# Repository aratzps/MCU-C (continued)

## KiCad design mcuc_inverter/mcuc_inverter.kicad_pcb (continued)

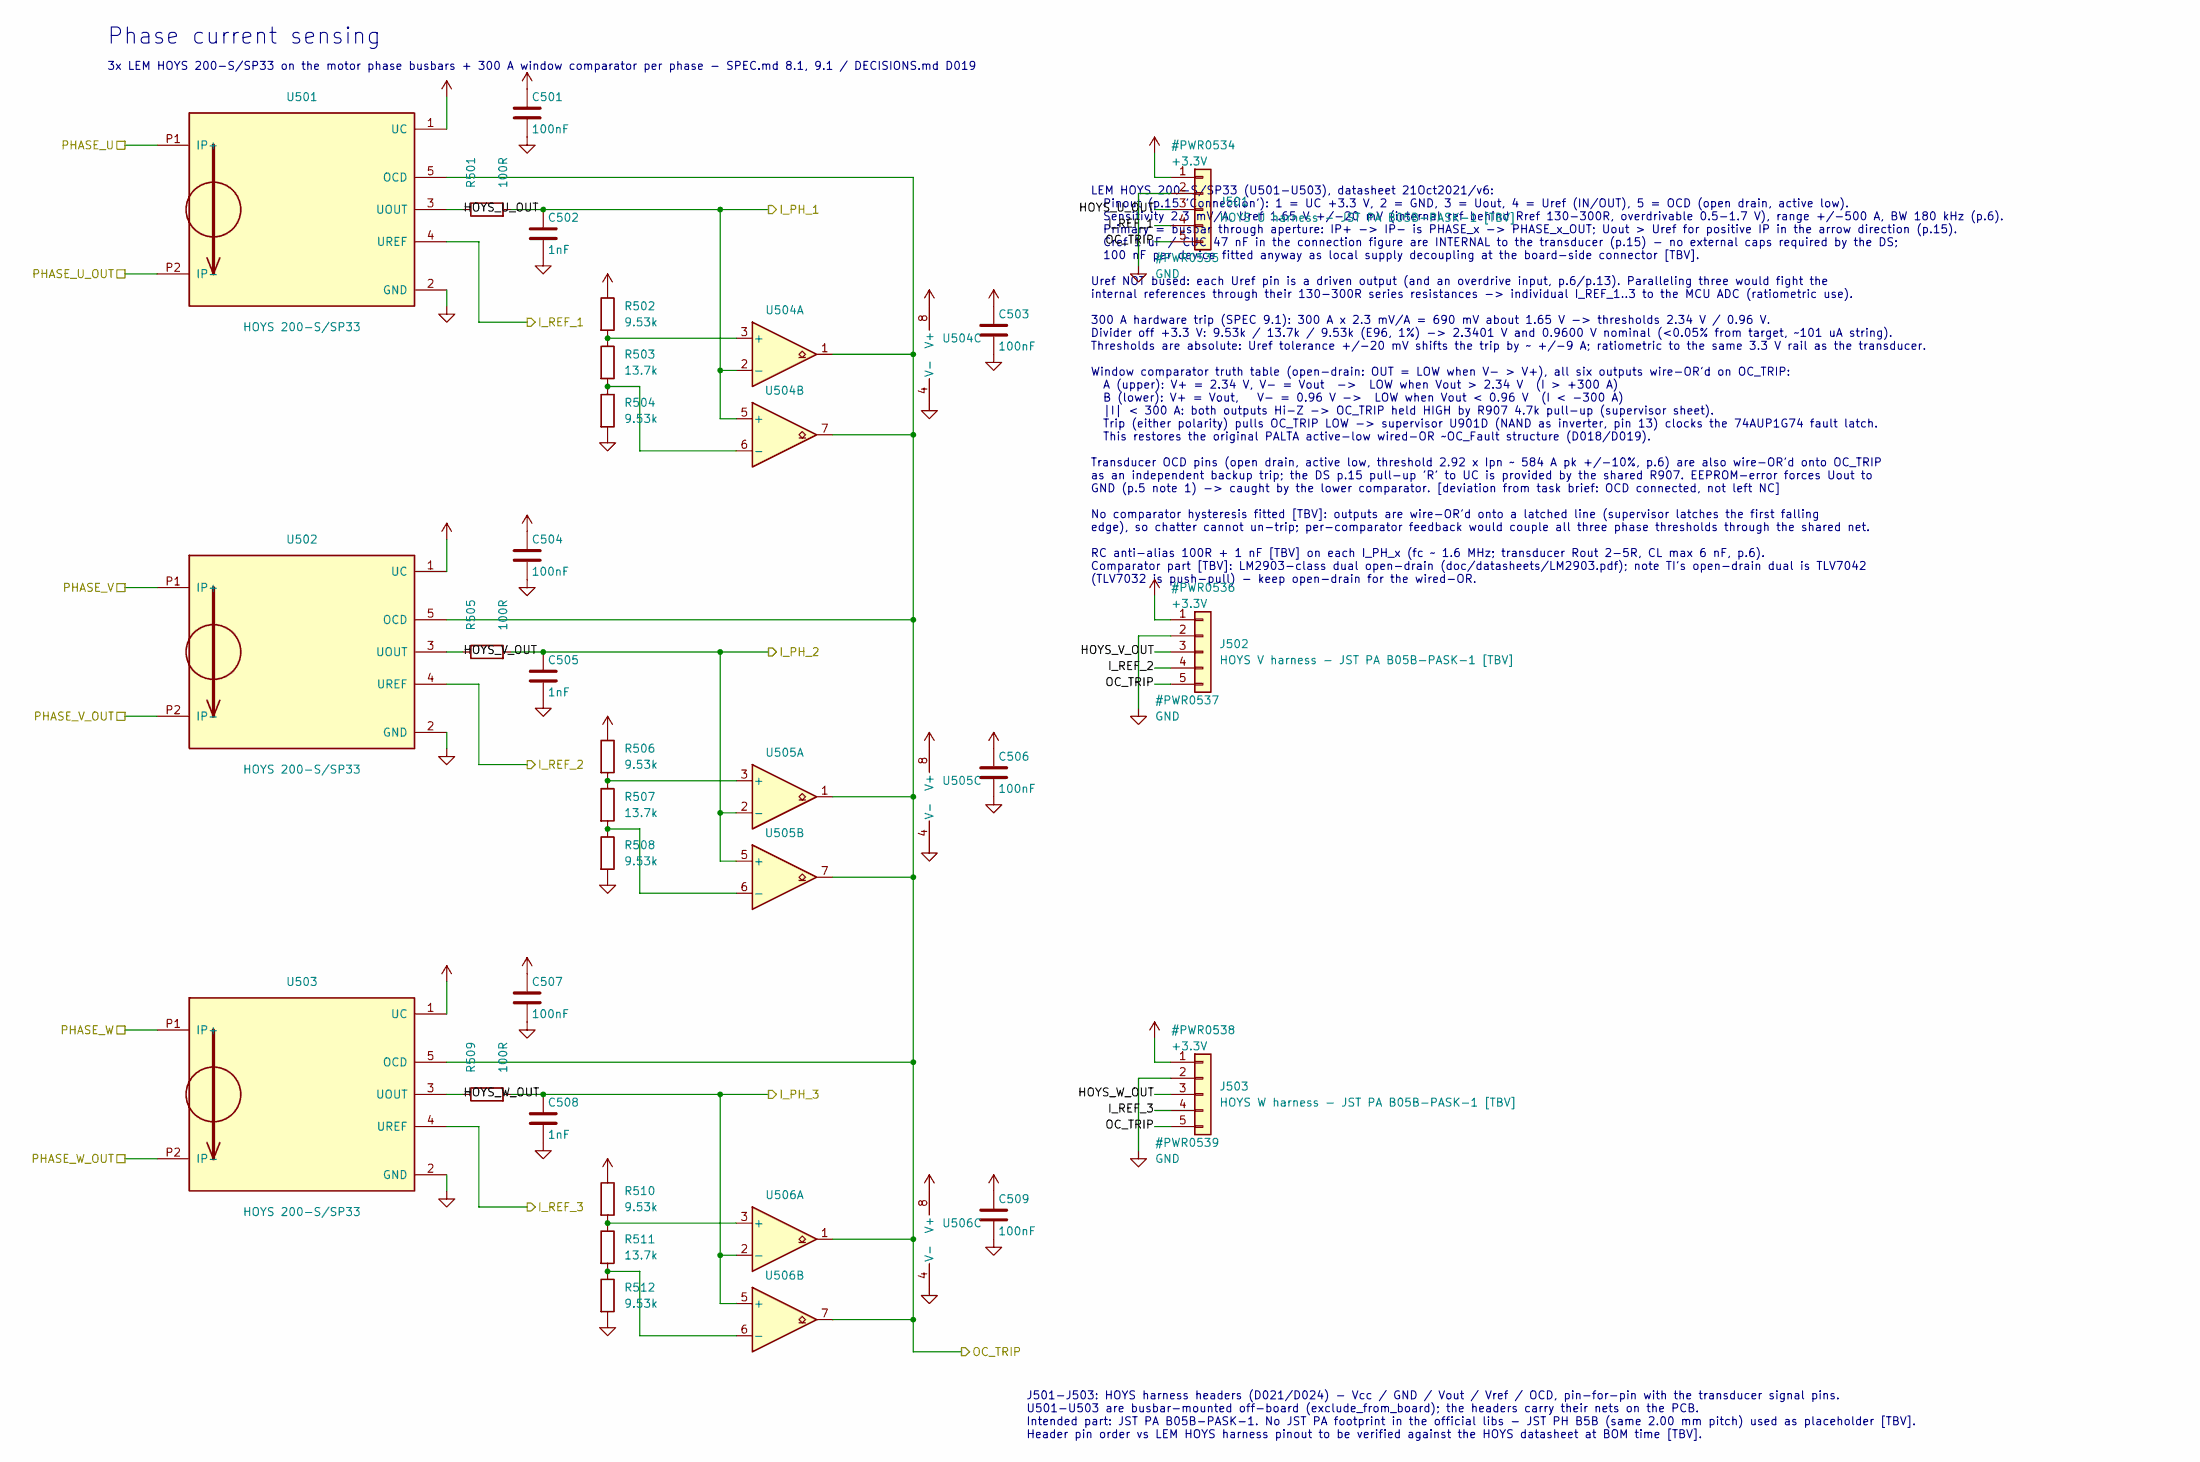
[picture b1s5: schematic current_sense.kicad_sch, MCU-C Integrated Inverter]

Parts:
C501, C503, C504, C506, C507, C509: 100nF; C_0603_1608Metric
C502, C505, C508: 1nF; C_0603_1608Metric
J501: HOYS U harness - JST PA B05B-PASK-1 [TBV]; JST_PH_B5B-PH-K_1x05_P2.00mm_Vertical
J502: HOYS V harness - JST PA B05B-PASK-1 [TBV]; JST_PH_B5B-PH-K_1x05_P2.00mm_Vertical
J503: HOYS W harness - JST PA B05B-PASK-1 [TBV]; JST_PH_B5B-PH-K_1x05_P2.00mm_Vertical
R501, R505, R509: 100R; R_0603_1608Metric
R502, R504, R506, R508, R510, R512: 9.53k; R_0603_1608Metric
R503, R507, R511: 13.7k; R_0603_1608Metric
U501, U502, U503: HOYS 200-S/SP33
U504, U505, U506: TLV7032/LM2903-class open-drain [TBV]; SOIC-8_3.9x4.9mm_P1.27mm

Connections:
/I_PH_1: C502.1, R501.2, U504.2 (-), U504.5 (+); also elsewhere on the board
/I_PH_2: C505.1, R505.2, U505.2 (-), U505.5 (+); also elsewhere on the board
/I_PH_3: C508.1, R509.2, U506.2 (-), U506.5 (+); also elsewhere on the board
/Phase current sensing/HOYS_U_OUT: J501.3, R501.1, U501.3 (UOUT); also elsewhere on the board
/Phase current sensing/HOYS_U_REF: J501.4; also elsewhere on the board
/Phase current sensing/HOYS_V_OUT: J502.3, R505.1, U502.3 (UOUT); also elsewhere on the board
/Phase current sensing/HOYS_V_REF: J502.4; also elsewhere on the board
/Phase current sensing/HOYS_W_OUT: J503.3, R509.1, U503.3 (UOUT); also elsewhere on the board
/Phase current sensing/HOYS_W_REF: J503.4; also elsewhere on the board
/Phase current sensing/OC_TRIP: J501.5, J502.5, J503.5, U501.5 (OCD), U502.5 (OCD), U503.5 (OCD), U504.1, U504.7, U505.1, U505.7, U506.1, U506.7; also elsewhere on the board
GND: C501.2, C502.2, C503.2, C504.2, C505.2, C506.2, C507.2, C508.2, C509.2, J501.2, J502.2, J503.2, R504.2, R508.2, R512.2, U501.2 (GND), U502.2 (GND), U503.2 (GND), U504.4 (V-), U505.4 (V-), U506.4 (V-); also elsewhere on the board
unnamed: R503.2, R504.1, U504.6 (-)
unnamed: R507.2, R508.1, U505.6 (-)
unnamed: R511.2, R512.1, U506.6 (-)

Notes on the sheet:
Phase current sensing
3x LEM HOYS 200-S/SP33 on the motor phase busbars + 300 A window comparator per phase - SPEC.md 8.1, 9.1 / DECISIONS.md D019
LEM HOYS 200-S/SP33 (U501-U503), datasheet 21Oct2021/v6: Pinout (p.15 'Connection'): 1 = UC +3.3 V, 2 = GND, 3 = Uout, 4 = Uref (IN/OUT), 5 = OCD (open drain, active low). Sensitivity 2.3 mV/A, Uref 1.65 V +/-20 mV (internal ref behind Rref 130-300R, overdrivable 0.5-1.7 V), range +/-500 A, BW 180 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
J501-J503: HOYS harness headers (D021/D024) - Vcc / GND / Vout / Vref / OCD, pin-for-pin with the transducer signal pins. U501-U503 are busbar-mounted off-board (exclude_from_board); the headers carry their nets on the PCB. Intended part: JST PA B05B-PASK-1. No JST PA footprint in the official libs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

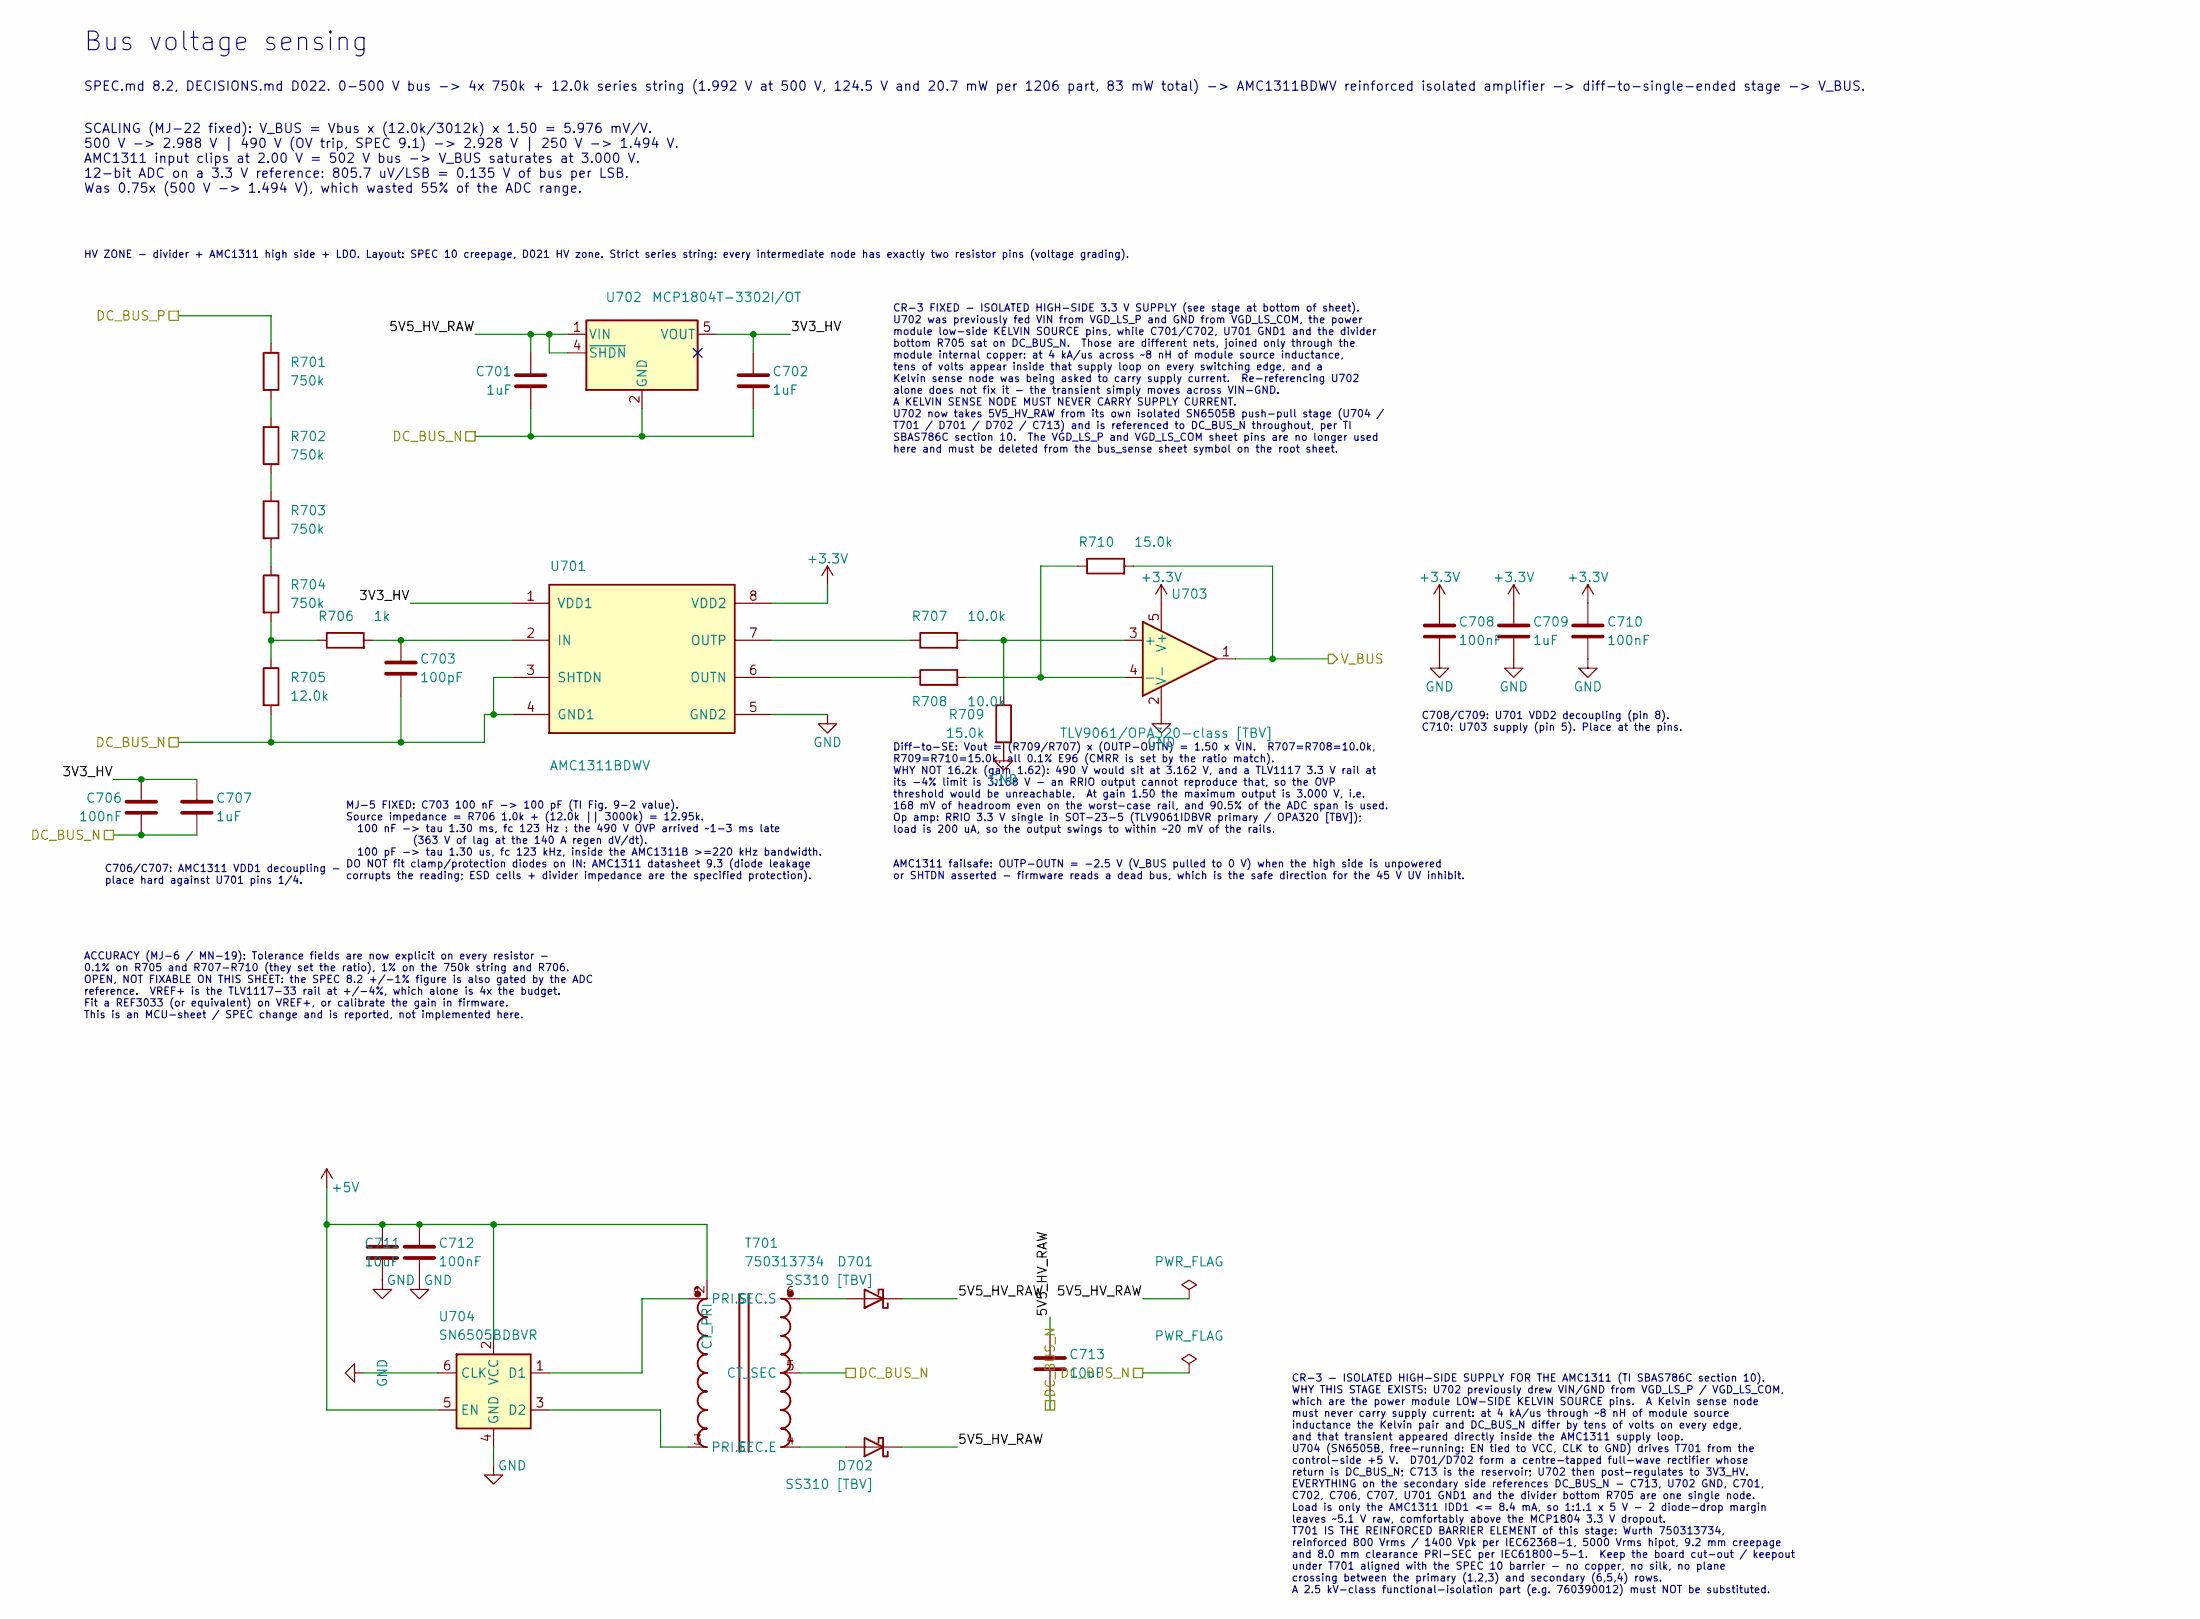
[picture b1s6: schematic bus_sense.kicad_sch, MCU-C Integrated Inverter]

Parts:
C701, C702, C707, C709: 1uF; C_0603_1608Metric
C703: 100pF; C_0603_1608Metric
C706, C708, C710, C712: 100nF; C_0603_1608Metric
C711, C713: 10uF; C_0805_2012Metric
D701, D702: SS310 [TBV]; D_SMC
R701, R702, R703, R704: 750k; R_1206_3216Metric; Tolerance 1%
R705: 12.0k; R_0603_1608Metric; Tolerance 0.1%
R706: 1k; R_0603_1608Metric; Tolerance 1%
R707, R708: 10.0k; R_0603_1608Metric; Tolerance 0.1%
R709, R710: 15.0k; R_0603_1608Metric; Tolerance 0.1%
T701: 750313734; WE_750313734; MPN 750313734
U701: AMC1311BDWV; SOIC-8_7.5x5.85mm_P1.27mm
U702: MCP1804T-3302I/OT; SOT-23-5
U703: TLV9061/OPA320-class [TBV]; SOT-23-5
U704: SN6505BDBVR; SOT-23-6

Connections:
+5V: C711.1, C712.1, T701.2 (CT_PRI), U704.2 (VCC), U704.5 (EN); also elsewhere on the board
/Auxiliary power/DC_BUS_P: R701.1; also elsewhere on the board
/Bus voltage sensing/3V3_HV: C702.1, C706.1, C707.1, U701.1 (VDD1), U702.5 (VOUT)
/Bus voltage sensing/5V5_HV_RAW: C701.1, C713.1, D701.1 (K), D702.1 (K), U702.1 (VIN), U702.4 (~SHDN)
/Precharge and contactor/DC_BUS_N: C701.2, C702.2, C703.2, C706.2, C707.2, C713.2, R705.2, T701.5 (CT_SEC), U701.3 (SHTDN), U701.4 (GND1), U702.2 (GND); also elsewhere on the board
/V_BUS: R710.2, U703.1; also elsewhere on the board
GND: C708.2, C709.2, C710.2, C711.2, C712.2, R709.2, U701.5 (GND2), U703.2 (V-), U704.4 (GND), U704.6 (CLK); also elsewhere on the board
unnamed: D701.2 (A), T701.6 (SEC.S)
unnamed: D702.2 (A), T701.4 (SEC.E)
unnamed: R701.2, R702.1
unnamed: R702.2, R703.1
unnamed: R703.2, R704.1
unnamed: R704.2, R705.1, R706.1
unnamed: T701.3 (PRI.E), U704.3 (D2)
unnamed: T701.1 (PRI.S), U704.1 (D1)
unnamed: C703.1, R706.2, U701.2 (IN)
unnamed: R708.1, U701.6 (OUTN)
unnamed: R707.1, U701.7 (OUTP)
unnamed: R707.2, R709.1, U703.3 (+)
unnamed: R708.2, R710.1, U703.4 (-)

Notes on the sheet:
Bus voltage sensing
SPEC.md 8.2, DECISIONS.md D022. 0-500 V bus -> 4x 750k + 12.0k series string (1.992 V at 500 V, 124.5 V and 20.7 mW per 1206 part, 83 mW total) -> AMC1311BDWV reinforced isolated amplifier -> diff-to-single-ended stage -> V_BUS.
HV ZONE - divider + AMC1311 high side + LDO. Layout: SPEC 10 creepage, D021 HV zone. Strict series string: every intermediate node has exactly two resistor pins (voltage grading).
C706/C707: AMC1311 VDD1 decoupling - place hard against U701 pins 1/4.
C708/C709: U701 VDD2 decoupling (pin 8). C710: U703 supply (pin 5). Place at the pins.
AMC1311 failsafe: OUTP-OUTN = -2.5 V (V_BUS pulled to 0 V) when the high side is unpowered or SHTDN asserted - firmware reads a dead bus, which is the safe direction for the 45 V UV inhibit.
SCALING (MJ-22 fixed): V_BUS = Vbus x (12.0k/3012k) x 1.50 = 5.976 mV/V. 500 V -> 2.988 V | 490 V (OV trip, SPEC 9.1) -> 2.928 V | 250 V -> 1.494 V. AMC1311 input clips at 2.00 V = 502 V bus -> V_BUS saturates at 3.000 V. 12-bit ADC on a 3.3 V reference: 805.7 uV/LSB = 0.135 V of bus per LSB. Was 0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
MJ-5 FIXED: C703 100 nF -> 100 pF (TI Fig. 9-2 value). Source impedance = R706 1.0k + (12.0k || 3000k) = 12.95k. 100 nF -> tau 1.30 ms, fc 123 Hz : the 490 V OVP arrived ~1-3 ms late (363 V of lag at the 140 A regen dV/dt). 100 pF -> tau 1.30 us, fc 123 kHz, inside the AMC1311B >=220 kHz bandwidth.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
Diff-to-SE: Vout = (R709/R707) x (OUTP-OUTN) = 1.50 x VIN. R707=R708=10.0k, R709=R710=15.0k, all 0.1% E96 (CMRR is set by the ratio match). WHY NOT 16.2k (gain 1.62): 490 V would sit at 3.162 V, and a TLV1117 3.3 V rail at its -4% limit is 3.168 V - an RRIO output cannot reproduce that, so the OVP 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
ACCURACY (MJ-6 / MN-19): Tolerance fields are now explicit on every resistor - 0.1% on R705 and R707-R710 (they set the ratio), 1% on the 750k string and R706. OPEN, NOT FIXABLE ON THIS SHEET: the SPEC 8.2 +/-1% figure is also gated by the ADC reference. VREF+ is the TLV1117-33 rail at +/-4%, which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
CR-3 FIXED - ISOLATED HIGH-SIDE 3.3 V SUPPLY (see stage at bottom of sheet). U702 was previously fed VIN from VGD_LS_P and GND from VGD_LS_COM, the power module low-side KELVIN SOURCE pins, while C701/C702, U701 GND1 and the divider bottom R705 sat on DC_BUS_N. Those are different nets, joined only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
CR-3 - ISOLATED HIGH-SIDE SUPPLY FOR THE AMC1311 (TI SBAS786C section 10). WHY THIS STAGE EXISTS: U702 previously drew VIN/GND from VGD_LS_P / VGD_LS_COM, which are the power module LOW-SIDE KELVIN SOURCE pins. A Kelvin sense node must never carry supply current: at 4 kA/us through ~8 nH of module 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

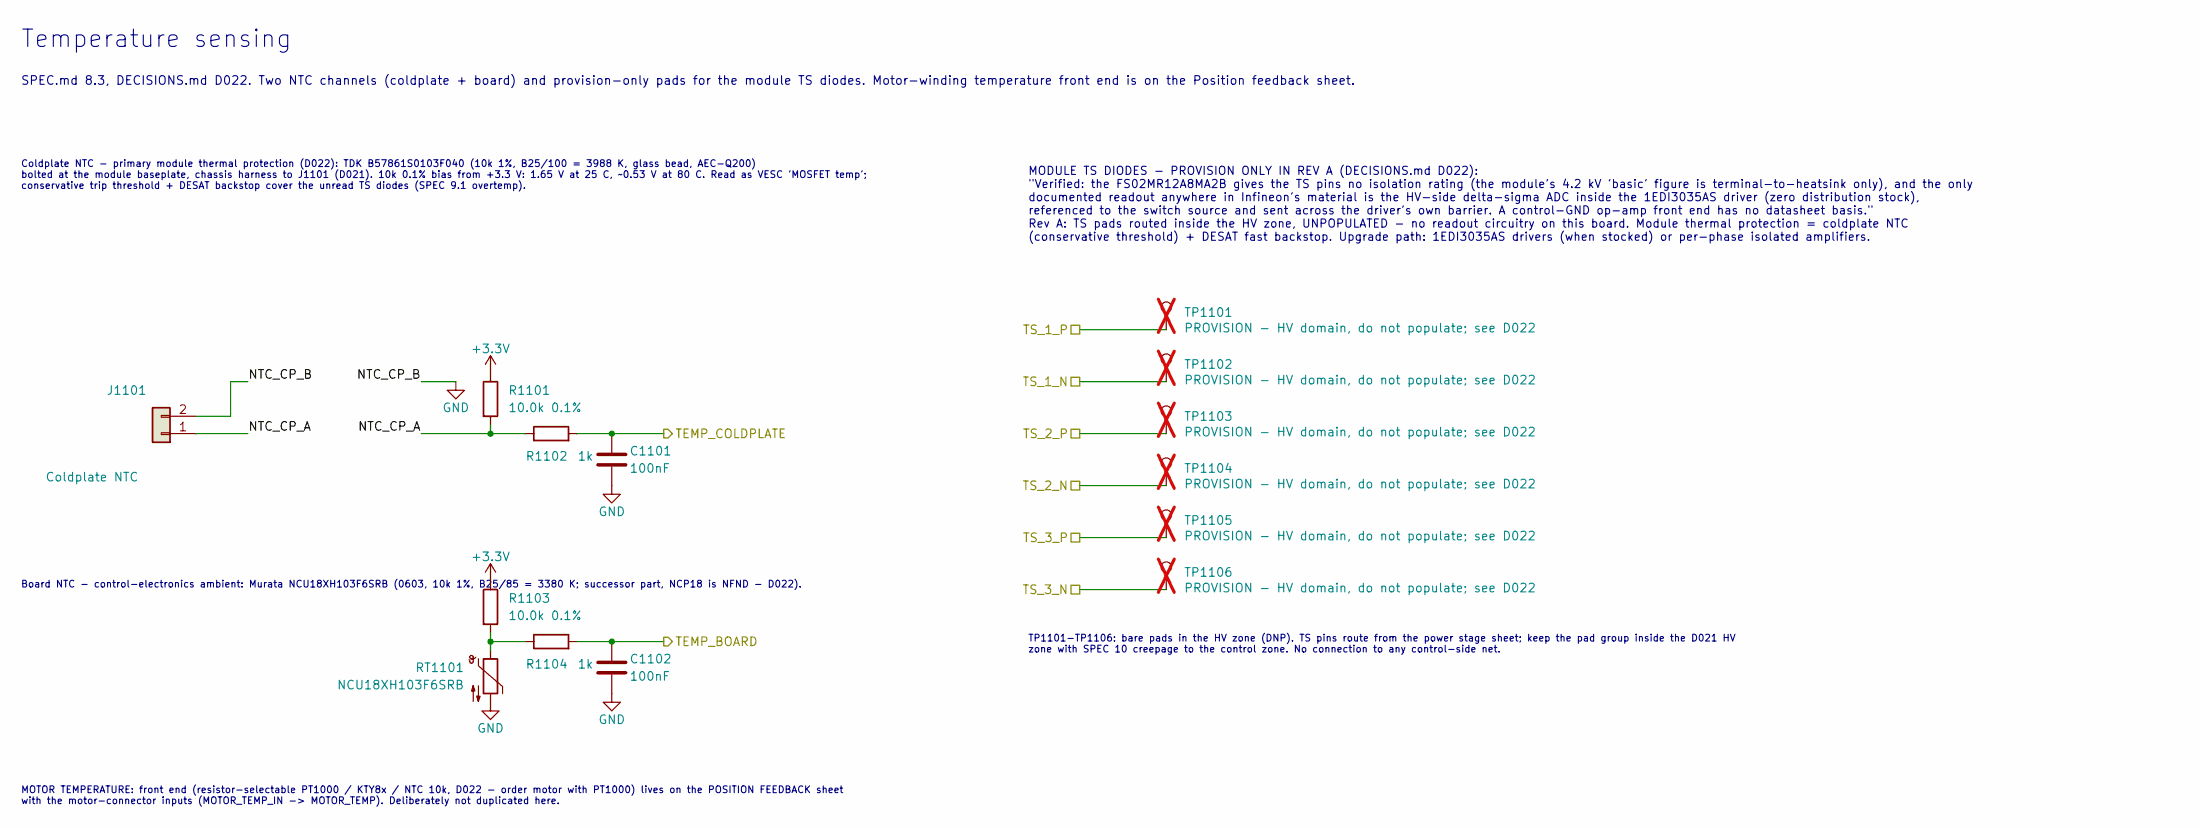
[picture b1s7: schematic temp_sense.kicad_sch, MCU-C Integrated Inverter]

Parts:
C1101, C1102: 100nF; C_0603_1608Metric
J1101: Coldplate NTC; JST_PH_B2B-PH-K_1x02_P2.00mm_Vertical
R1101, R1103: 10.0k 0.1%; R_0603_1608Metric
R1102, R1104: 1k; R_0603_1608Metric
RT1101: NCU18XH103F6SRB; R_0603_1608Metric
TP1101, TP1102, TP1103, TP1104, TP1105, TP1106: PROVISION - HV domain, do not populate; see D022; TestPoint_Pad_D1.5mm; not fitted

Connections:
/TEMP_BOARD: C1102.1, R1104.2; also elsewhere on the board
/TEMP_COLDPLATE: C1101.1, R1102.2; also elsewhere on the board
/TS_1_N: TP1102.1; also elsewhere on the board
/TS_1_P: TP1101.1; also elsewhere on the board
/TS_2_N: TP1104.1; also elsewhere on the board
/TS_2_P: TP1103.1; also elsewhere on the board
/TS_3_N: TP1106.1; also elsewhere on the board
/TS_3_P: TP1105.1; also elsewhere on the board
/Temperature sensing/NTC_CP_A: J1101.1, R1101.2, R1102.1
GND: C1101.2, C1102.2, J1101.2, RT1101.2; also elsewhere on the board
unnamed: R1103.2, R1104.1, RT1101.1

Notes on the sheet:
Temperature sensing
SPEC.md 8.3, DECISIONS.md D022. Two NTC channels (coldplate + board) and provision-only pads for the module TS diodes. Motor-winding temperature front end is on the Position feedback sheet.
Coldplate NTC - primary module thermal protection (D022): TDK B57861S0103F040 (10k 1%, B25/100 = 3988 K, glass bead, AEC-Q200) bolted at the module baseplate, chassis harness to J1101 (D021). 10k 0.1% bias from +3.3 V: 1.65 V at 25 C, ~0.53 V at 80 C. Read as VESC 'MOSFET temp'; conservative trip t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
Board NTC - control-electronics ambient: Murata NCU18XH103F6SRB (0603, 10k 1%, B25/85 = 3380 K; successor part, NCP18 is NFND - D022).
MODULE TS DIODES - PROVISION ONLY IN REV A (DECISIONS.md D022): "Verified: the FS02MR12A8MA2B gives the TS pins no isolation rating (the module's 4.2 kV 'basic' figure is terminal-to-heatsink only), and the only documented readout anywhere in Infineon's material is the HV-side delta-sigma ADC insid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
TP1101-TP1106: bare pads in the HV zone (DNP). TS pins route from the power stage sheet; keep the pad group inside the D021 HV zone with SPEC 10 creepage to the control zone. No connection to any control-side net.
MOTOR TEMPERATURE: front end (resistor-selectable PT1000 / KTY8x / NTC 10k, D022 - order motor with PT1000) lives on the POSITION FEEDBACK sheet with the motor-connector inputs (MOTOR_TEMP_IN -> MOTOR_TEMP). Deliberately not duplicated here.

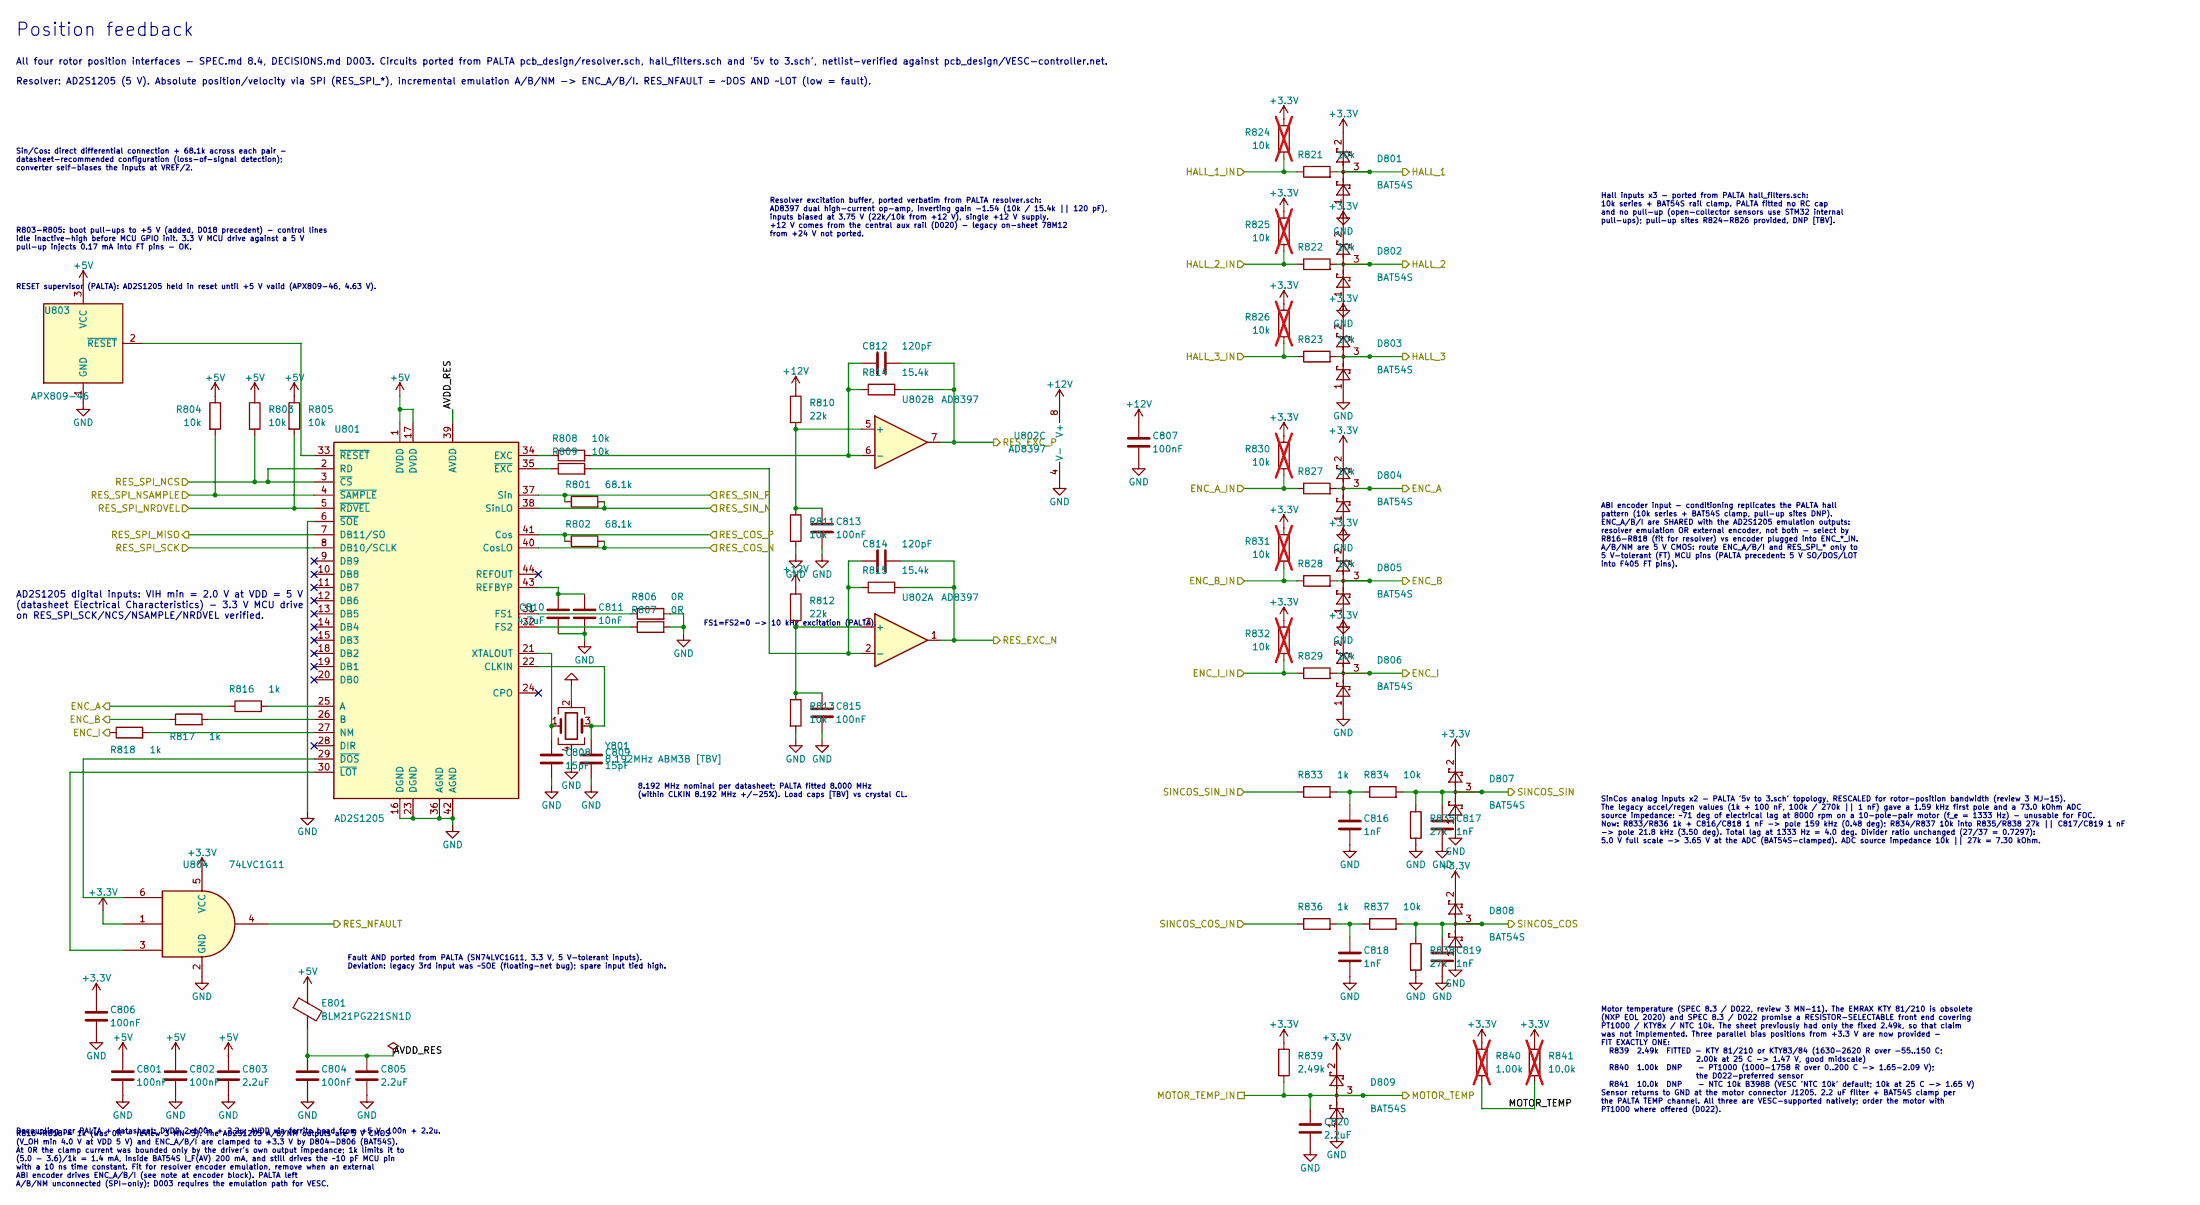
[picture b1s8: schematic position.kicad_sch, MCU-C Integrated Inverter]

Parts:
C801, C802, C804, C806, C807, C813, C815: 100nF; C_0603_1608Metric
C803, C805, C820: 2.2uF; C_0603_1608Metric
C808, C809: 15pF; C_0603_1608Metric
C810: 4.7uF; C_0603_1608Metric
C811: 10nF; C_0603_1608Metric
C812, C814: 120pF; C_0603_1608Metric
C816, C817, C818, C819: 1nF; C_0603_1608Metric
D801, D802, D803, D804, D805, D806, D807, D808, D809: BAT54S; SOT-23
E801: BLM21PG221SN1D; L_0805_2012Metric
R801, R802: 68.1k; R_0603_1608Metric
R803, R804, R805, R808, R809, R811, R813, R821, R822, R823, R827, R828, R829, R834, R837: 10k; R_0603_1608Metric
R806, R807: 0R; R_0603_1608Metric
R810, R812: 22k; R_0603_1608Metric
R814, R815: 15.4k; R_0603_1608Metric
R816, R817, R818, R833, R836: 1k; R_0603_1608Metric
R824, R825, R826, R830, R831, R832: 10k; R_0603_1608Metric; not fitted
R835, R838: 27k; R_0603_1608Metric
R839: 2.49k; R_0603_1608Metric
R840: 1.00k; R_0603_1608Metric; not fitted
R841: 10.0k; R_0603_1608Metric; not fitted
U801: AD2S1205; LQFP-44_10x10mm_P0.8mm
U802: AD8397; SOIC-8-1EP_3.9x4.9mm_P1.27mm_EP2.29x3mm
U803: APX809-46; SOT-23
U804: 74LVC1G11; SOT-363_SC-70-6
Y801: 8.192MHz ABM3B [TBV]; Crystal_SMD_Abracon_ABM3B-4Pin_5.0x3.2mm

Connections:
+5V: C801.1, C802.1, C803.1, E801.1, R803.1, R804.1, R805.1, U801.1 (DVDD), U801.17 (DVDD), U803.3 (VCC); also elsewhere on the board
+12V: C807.1, R810.1, R812.1, U802.8 (V+); also elsewhere on the board
/Communications/ENC_A_IN: R827.1, R830.2; also elsewhere on the board
/Communications/ENC_B_IN: R828.1, R831.2; also elsewhere on the board
/Communications/ENC_I_IN: R829.1, R832.2; also elsewhere on the board
/Communications/HALL_1_IN: R821.1, R824.2; also elsewhere on the board
/Communications/HALL_2_IN: R822.1, R825.2; also elsewhere on the board
/Communications/HALL_3_IN: R823.1, R826.2; also elsewhere on the board
/Communications/RES_COS_N: R802.2, U801.40 (CosLO); also elsewhere on the board
/Communications/RES_COS_P: R802.1, U801.41 (Cos); also elsewhere on the board
/Communications/RES_EXC_N: C814.2, R815.2, U802.1; also elsewhere on the board
/Communications/RES_EXC_P: C812.2, R814.2, U802.7; also elsewhere on the board
/Communications/RES_SIN_N: R801.2, U801.38 (SinLO); also elsewhere on the board
/Communications/RES_SIN_P: R801.1, U801.37 (Sin); also elsewhere on the board
/Communications/SINCOS_COS_IN: R836.1; also elsewhere on the board
/Communications/SINCOS_SIN_IN: R833.1; also elsewhere on the board
/ENC_A: D804.3 (COM), R816.1, R827.2; also elsewhere on the board
/ENC_B: D805.3 (COM), R817.1, R828.2; also elsewhere on the board
/ENC_I: D806.3 (COM), R818.1, R829.2; also elsewhere on the board
/HALL_1: D801.3 (COM), R821.2; also elsewhere on the board
/HALL_2: D802.3 (COM), R822.2; also elsewhere on the board
/HALL_3: D803.3 (COM), R823.2; also elsewhere on the board
/MOTOR_TEMP: C820.1, D809.3 (COM), R839.2, R840.2, R841.2; also elsewhere on the board
/Position feedback/AVDD_RES: C804.1, C805.1, E801.2, U801.39 (AVDD)
/RES_NFAULT: U804.4; also elsewhere on the board
/RES_SPI_MISO: U801.7 (DB11/SO); also elsewhere on the board
/RES_SPI_NCS: R803.2, U801.2 (RD), U801.3 (~CS); also elsewhere on the board
/RES_SPI_NRDVEL: R805.2, U801.5 (~RDVEL); also elsewhere on the board
/RES_SPI_NSAMPLE: R804.2, U801.4 (~SAMPLE); also elsewhere on the board
/RES_SPI_SCK: U801.8 (DB10/SCLK); also elsewhere on the board
/SINCOS_COS: C819.1, D808.3 (COM), R837.2, R838.1; also elsewhere on the board
/SINCOS_SIN: C817.1, D807.3 (COM), R834.2, R835.1; also elsewhere on the board
GND: C801.2, C802.2, C803.2, C804.2, C805.2, C806.2, C807.2, C808.2, C809.2, C810.2, C811.2, C813.2, C815.2, C816.2, C817.2, C818.2, C819.2, C820.2, D801.1 (A), D802.1 (A), D803.1 (A), D804.1 (A), D805.1 (A), D806.1 (A), D807.1 (A), D808.1 (A), D809.1 (A), R806.2, R807.2, R811.2, R813.2, R835.2, R838.2, U801.6 (~SOE), U801.16 (DGND), U801.23 (DGND), U801.36 (AGND), U801.42 (AGND), U802.4 (V-), U803.1 (GND), U804.2 (GND), Y801.2, Y801.4; also elsewhere on the board
unnamed: C816.1, R833.2, R834.1
unnamed: C818.1, R836.2, R837.1
unnamed: R816.2, U801.25 (A)
unnamed: R817.2, U801.26 (B)
unnamed: C809.1, U801.22 (CLKIN), Y801.3
unnamed: R808.1, U801.34 (EXC)
unnamed: R806.1, U801.31 (FS1)
unnamed: R807.1, U801.32 (FS2)
unnamed: R818.2, U801.27 (NM)
unnamed: C810.1, C811.1, U801.43 (REFBYP)
unnamed: C808.1, U801.21 (XTALOUT), Y801.1
unnamed: U801.29 (~DOS), U804.6
unnamed: R809.1, U801.35 (~EXC)
unnamed: U801.30 (~LOT), U804.3
unnamed: U801.33 (~RESET), U803.2 (~RESET)
unnamed: C815.1, R812.2, R813.1, U802.3 (+)
unnamed: C814.1, R809.2, R815.1, U802.2 (-)
unnamed: C813.1, R810.2, R811.1, U802.5 (+)
unnamed: C812.1, R808.2, R814.1, U802.6 (-)

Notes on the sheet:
Position feedback
All four rotor position interfaces - SPEC.md 8.4, DECISIONS.md D003. Circuits ported from PALTA pcb_design/resolver.sch, hall_filters.sch and '5v to 3.sch', netlist-verified against pcb_design/VESC-controller.net.
Resolver: AD2S1205 (5 V). Absolute position/velocity via SPI (RES_SPI_*), incremental emulation A/B/NM -> ENC_A/B/I. RES_NFAULT = ~DOS AND ~LOT (low = fault).
RESET supervisor (PALTA): AD2S1205 held in reset until +5 V valid (APX809-46, 4.63 V).
R803-R805: boot pull-ups to +5 V (added, D018 precedent) - control lines idle inactive-high before MCU GPIO init. 3.3 V MCU drive against a 5 V pull-up injects 0.17 mA into FT pins - OK.
R816-R818 = 1k (was 0R - review 3 MN-3). The AD2S1205 A/B/NM outputs are 5 V CMOS (V_OH min 4.0 V at VDD 5 V) and ENC_A/B/I are clamped to +3.3 V by D804-D806 (BAT54S). At 0R the clamp current was bounded only by the driver's own output impedance; 1k limits it to (5.0 - 3.6)/1k = 1.4 mA, inside BAT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
Fault AND ported from PALTA (SN74LVC1G11, 3.3 V, 5 V-tolerant inputs). Deviation: legacy 3rd input was ~SOE (floating-net bug); spare input tied high.
Decoupling per PALTA + datasheet: DVDD 2x100n + 2.2u; AVDD via ferrite bead from +5 V, 100n + 2.2u.
Sin/Cos: direct differential connection + 68.1k across each pair - datasheet-recommended configuration (loss-of-signal detection); converter self-biases the inputs at VREF/2.
FS1=FS2=0 -> 10 kHz excitation (PALTA).
8.192 MHz nominal per datasheet; PALTA fitted 8.000 MHz (within CLKIN 8.192 MHz +/-25%). Load caps [TBV] vs crystal CL.
Resolver excitation buffer, ported verbatim from PALTA resolver.sch: AD8397 dual high-current op-amp, inverting gain -1.54 (10k / 15.4k || 120 pF), inputs biased at 3.75 V (22k/10k from +12 V), single +12 V supply. +12 V comes from the central aux rail (D020) - legacy on-sheet 78M12 from +24 V not 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
Hall inputs x3 - ported from PALTA hall_filters.sch: 10k series + BAT54S rail clamp. PALTA fitted no RC cap and no pull-up (open-collector sensors use STM32 internal pull-ups); pull-up sites R824-R826 provided, DNP [TBV].
ABI encoder input - conditioning replicates the PALTA hall pattern (10k series + BAT54S clamp, pull-up sites DNP). ENC_A/B/I are SHARED with the AD2S1205 emulation outputs: resolver emulation OR external encoder, not both - select by R816-R818 (fit for resolver) vs encoder plugged into ENC_*_IN. A/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
SinCos analog inputs x2 - PALTA '5v to 3.sch' topology, RESCALED for rotor-position bandwidth (review 3 MJ-15). The legacy accel/regen values (1k + 100 nF, 100k / 270k || 1 nF) gave a 1.59 kHz first pole and a 73.0 kOhm ADC source impedance: ~71 deg of electrical lag at 8000 rpm on a 10-pole-pair m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
Motor temperature (SPEC 8.3 / D022, review 3 MN-11). The EMRAX KTY 81/210 is obsolete (NXP EOL 2020) and SPEC 8.3 / D022 promise a RESISTOR-SELECTABLE front end covering PT1000 / KTY8x / NTC 10k. The sheet previously had only the fixed 2.49k, so that claim was not implemented. Three parallel bias p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
AD2S1205 digital inputs: VIH min = 2.0 V at VDD = 5 V (datasheet Electrical Characteristics) - 3.3 V MCU drive on RES_SPI_SCK/NCS/NSAMPLE/NRDVEL verified.

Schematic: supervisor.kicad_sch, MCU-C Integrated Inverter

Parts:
C901, C902, C903, C904: 100nF; C_0603_1608Metric
C905: 220pF; C_0603_1608Metric
C906: 100n; C_0603_1608Metric
C907: 220n; C_0603_1608Metric
D901: BAT54S; SOT-23
D902: APT2012SURCK red (OCP); LED_0805_2012Metric
D903: APT2012SYCK amber (DRV FLT); LED_0805_2012Metric
D904: BAT54WS; D_SOD-323
R901, R902, R903, R904, R905, R906, R907, R908, R913, R914: 4.7k; R_0603_1608Metric
R909: 10k; R_0603_1608Metric
R910: 22R; R_0603_1608Metric
R911, R912: 2.2k; R_0603_1608Metric
U901: SN74LVC00APWR; TSSOP-14_4.4x5mm_P0.65mm
U902, U903: SN74ALVC08PWR; TSSOP-14_4.4x5mm_P0.65mm
U904: SN74AUP1G74DCUR; VSSOP-8_2.3x2mm_P0.5mm

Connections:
/DRV_RST_IN: C907.1, R914.1, U903.12; also elsewhere on the board
/FAULT_RESET: C906.1, R913.1, U904.6 (~CLR); also elsewhere on the board
/Gate drive/DRV_RST_OUT: U903.11; also elsewhere on the board
/Gate drive/PWM_HS_1_GATED: U902.3; also elsewhere on the board
/Gate drive/PWM_HS_2_GATED: U902.8; also elsewhere on the board
/Gate drive/PWM_HS_3_GATED: U903.3; also elsewhere on the board
/Gate drive/PWM_LS_1_GATED: U902.6; also elsewhere on the board
/Gate drive/PWM_LS_2_GATED: U902.11; also elsewhere on the board
/Gate drive/PWM_LS_3_GATED: U903.6; also elsewhere on the board
/MCU/PWM_HS_1: R901.1, U901.1, U902.1; also elsewhere on the board
/MCU/PWM_HS_2: R903.1, U901.4, U902.9; also elsewhere on the board
/MCU/PWM_HS_3: R905.1, U901.9, U903.1; also elsewhere on the board
/MCU/PWM_LS_1: R902.1, U901.2, U902.5; also elsewhere on the board
/MCU/PWM_LS_2: R904.1, U901.5, U902.13; also elsewhere on the board
/MCU/PWM_LS_3: R906.1, U901.10, U903.5; also elsewhere on the board
/OC_LATCHED: U904.5 (Q); also elsewhere on the board
/Phase current sensing/OC_TRIP: R907.2, U901.13; also elsewhere on the board
/Supervisor and interlocks/DRV_FAULT_IN: D903.1 (K), R909.2, R910.1; also elsewhere on the board
/Supervisor and interlocks/FAULT_BKIN: C905.1, D901.3 (COM), D904.2 (A), R910.2; also elsewhere on the board
/Supervisor and interlocks/OC_LATCH_N: D902.1 (K), D904.1 (K), U903.13, U904.3 (~Q)
GND: C901.2, C902.2, C903.2, C904.2, C905.2, C906.2, C907.2, D901.1 (A), R901.2, R902.2, R903.2, R904.2, R905.2, R906.2, U901.7 (GND), U902.7 (GND), U903.7 (GND), U903.9, U903.10, U904.4 (GND); also elsewhere on the board
unnamed: D902.2 (A), R911.2
unnamed: D903.2 (A), R912.2
unnamed: R908.2, U901.12
unnamed: U901.3, U902.2, U902.4
unnamed: U901.6, U902.10, U902.12
unnamed: U901.8, U903.2, U903.4
unnamed: U901.11, U904.1 (C)

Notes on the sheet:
PWM overlap elimination (per phase: HS/LS pair gated by NAND of the pair)
Overcurrent latch + driver-fault conditioning + driver reset
Pulldowns hold gate-drive inputs low while MCU pins are Hi-Z during boot (as PALTA).
Ported from PALTA pcb_design/supervisor.sch (Monitor logic, rev 0.2) - SPEC.md 9.2 / DECISIONS.md D008 Logic (all 3.3 V): GATED_HS = HS AND NAND(HS,LS); GATED_LS = LS AND NAND(HS,LS) -> both low if HS,LS overlap OC latch: 74AUP1G74, D=1, CLK = NOT(OC_TRIP) (NAND U1D, spare input tied high via R8) Q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
U903 gate 3 is now SPARE (CR-1). Inputs tied low, output open. Available if a discharge / bus-live interlock needs a gate.
MJ-1: the 300 A overcurrent latch had NO path to TIM1_BKIN - it only reached the reset chain, so SPEC 9.2 was false as built. D904 pulls FAULT_BKIN low when OC_LATCH_N trips: 0.33 mA through R909 gives Vf ~0.28 V, so BKIN sits at ~0.31 V vs VIL 0.99 V. Reverse-biased when only a driver fault is pre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
